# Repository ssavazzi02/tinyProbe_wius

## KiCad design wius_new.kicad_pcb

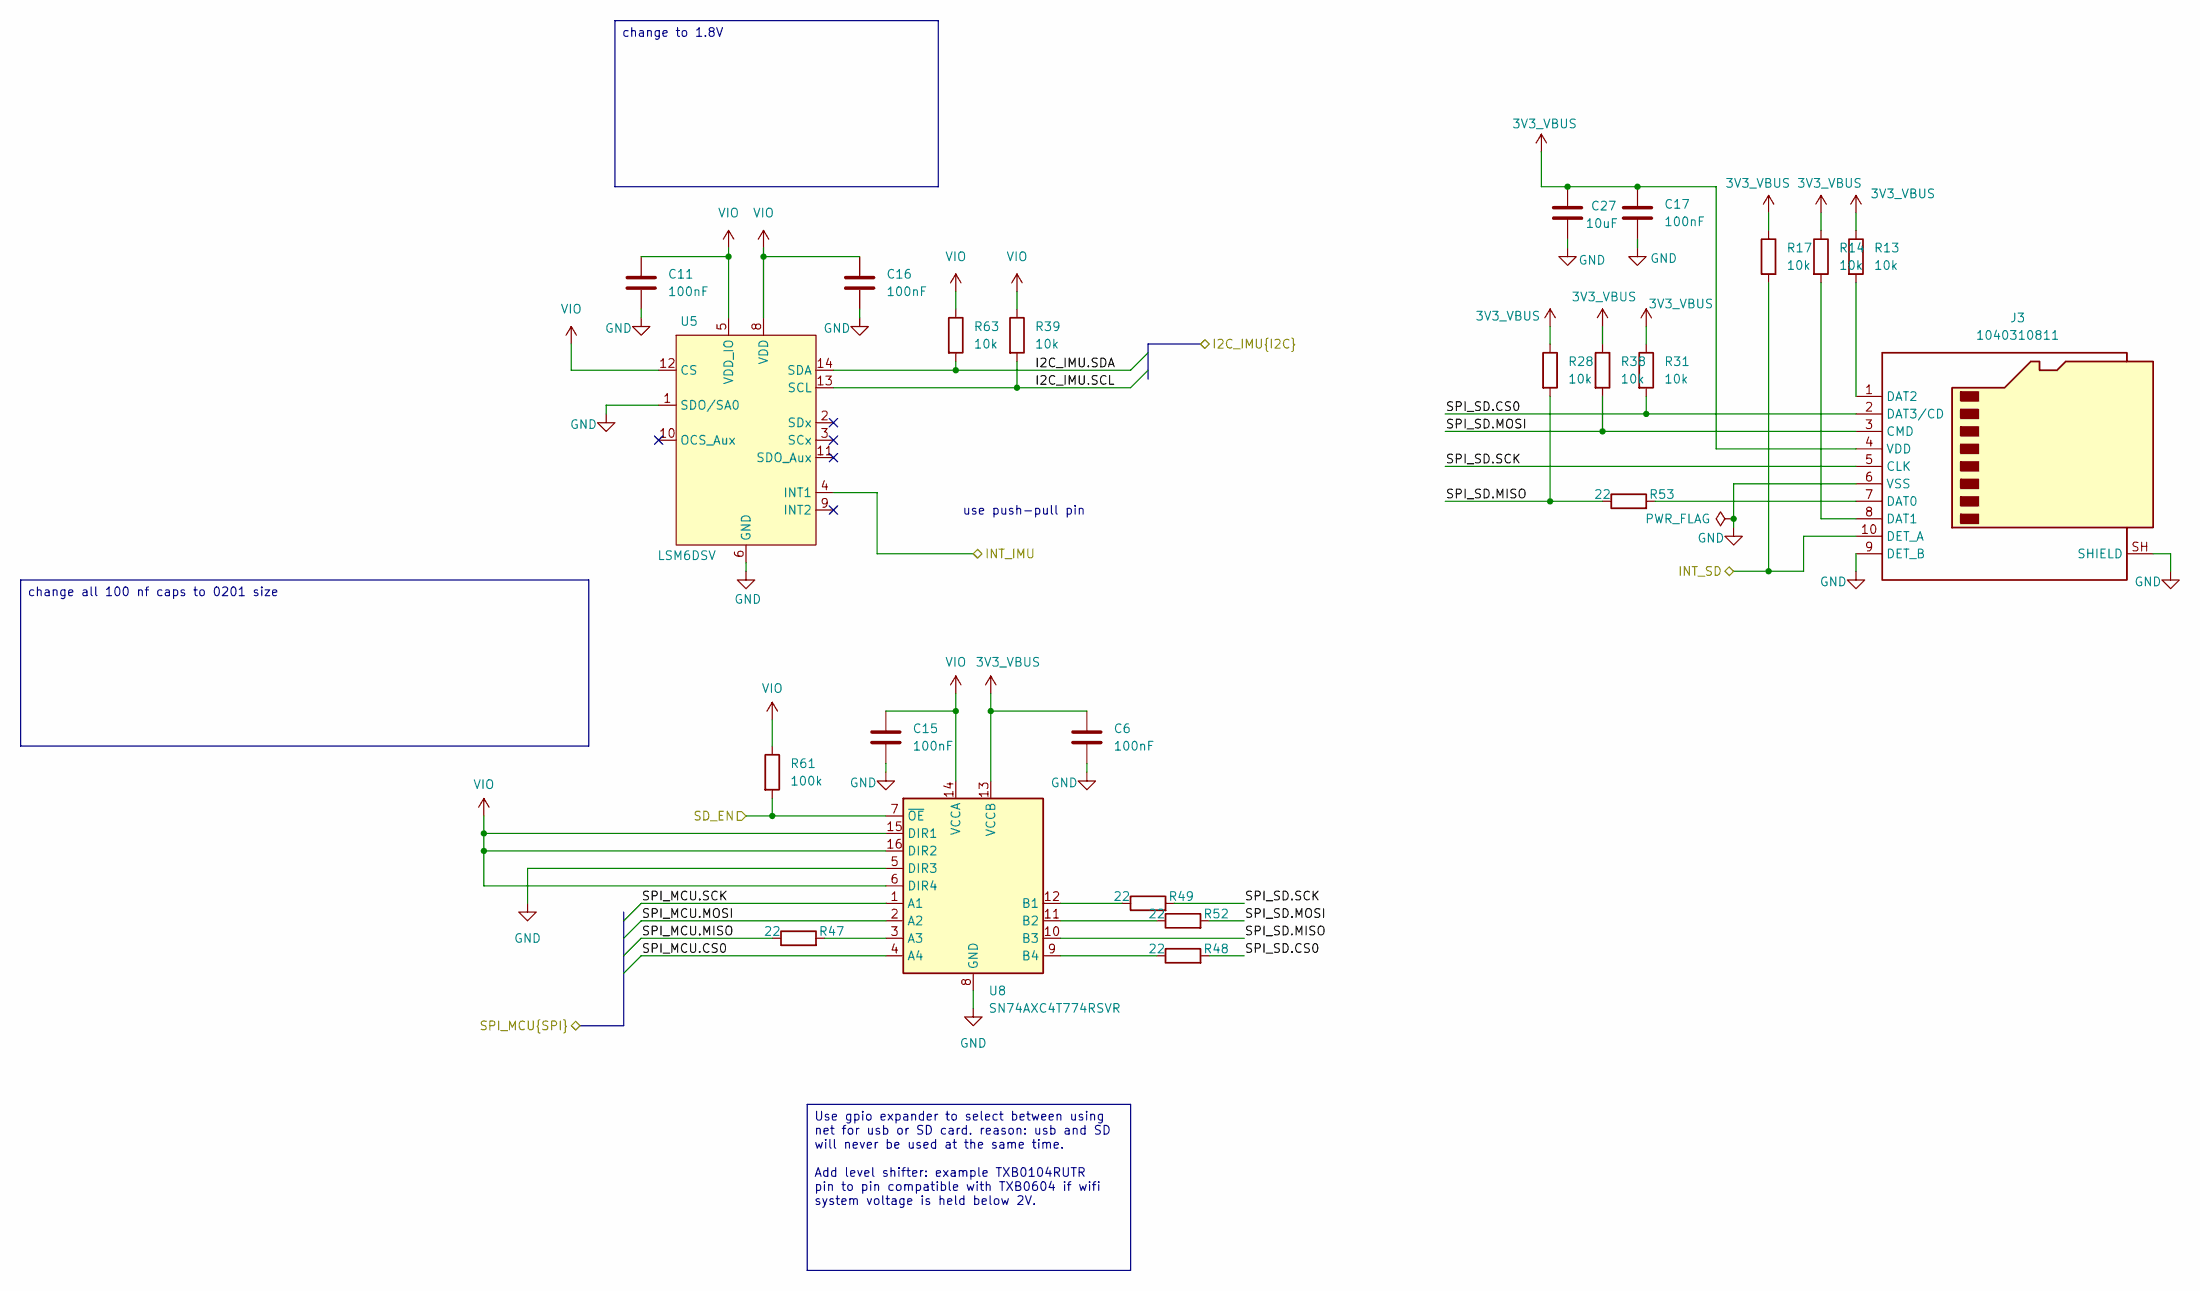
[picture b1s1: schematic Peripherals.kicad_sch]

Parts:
C6, C11, C15, C16, C17: 100nF; C_0201_0603Metric; Voltage 10V; Tolerance 20%; MPN GRM033R61A104ME15
C27: 10uF; C_0603_1608Metric; Voltage 10V; Tolerance 20%; MPN GRM188R61A106ME69; LCSC C197020603
J3: 1040310811; microSD_HC_Molex_104031-0811; MPN 1040310811; LCSC C585350
R13, R14, R17, R28, R31, R38, R39, R63: 10k; R_0201_0603Metric; Tolerance 1%; MPN ERJ-1GJF1002C; LCSC C20021044
R47, R48, R49, R52, R53: 22; R_0201_0603Metric; Tolerance 1%; MPN ERJ-1GJF22R0C; LCSC C20021234
R61: 100k; R_0201_0603Metric; Tolerance 1%; MPN ERJ-1GJF1003C; LCSC C20021045
U5: LSM6DSV; LGA-14_3x2.5mm_P0.5mm_LayoutBorder3x4y; MPN LSM6DSV; LCSC C5267399
U8: SN74AXC4T774RSVR; UQFN-16_1.8x2.6mm_P0.4mm; MPN SN74AXC4T774RSVR; LCSC C1849454

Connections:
3V3_VBUS: C6.1, C17.1, C27.1, J3.4 (VDD), R13.1, R14.1, R17.1, R28.1, R31.1, R38.1, U8.13 (VCCB); also elsewhere on the board
/IMU_SD/I2C_IMU.SCL: R39.2, U5.13 (SCL); also elsewhere on the board
/IMU_SD/I2C_IMU.SDA: R63.2, U5.14 (SDA); also elsewhere on the board
/IMU_SD/INT_IMU: U5.4 (INT1); also elsewhere on the board
/IMU_SD/INT_SD: J3.10 (DET_A), R17.2; also elsewhere on the board
/IMU_SD/SD_EN: R61.2, U8.7 (~OE); also elsewhere on the board
/IMU_SD/SPI_MCU.CS0: U8.4 (A4); also elsewhere on the board
/IMU_SD/SPI_MCU.MISO: R47.1; also elsewhere on the board
/IMU_SD/SPI_MCU.MOSI: U8.2 (A2); also elsewhere on the board
/IMU_SD/SPI_MCU.SCK: U8.1 (A1); also elsewhere on the board
/IMU_SD/SPI_SD.CS0: J3.2 (DAT3/CD), R31.2, R48.2
/IMU_SD/SPI_SD.MISO: R28.2, R53.1, U8.10 (B3)
/IMU_SD/SPI_SD.MOSI: J3.3 (CMD), R38.2, R52.2
/IMU_SD/SPI_SD.SCK: J3.5 (CLK), R49.2
GND: C6.2, C11.2, C15.2, C16.2, C17.2, C27.2, J3.6 (VSS), J3.9 (DET_B), J3.SH (SHIELD), U5.1 (SDO/SA0), U5.6 (GND), U5.7 (GND), U8.5 (DIR3), U8.8 (GND); also elsewhere on the board
unnamed: J3.7 (DAT0), R53.2
unnamed: J3.8 (DAT1), R14.2
unnamed: J3.1 (DAT2), R13.2
unnamed: R47.2, U8.3 (A3)
unnamed: R49.1, U8.12 (B1)
unnamed: R52.1, U8.11 (B2)
unnamed: R48.1, U8.9 (B4)
VIO: C11.1, C15.1, C16.1, R39.1, R61.1, R63.1, U5.5 (VDD_IO), U5.8 (VDD), U5.12 (CS), U8.6 (DIR4), U8.14 (VCCA), U8.15 (DIR1), U8.16 (DIR2); also elsewhere on the board

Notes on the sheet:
use push-pull pin
change to 1.8V
Use gpio expander to select between using net for usb or SD card. reason: usb and SD will never be used at the same time. Add level shifter: example TXB0104RUTR pin to pin compatible with TXB0604 if wifi system voltage is held below 2V.
change all 100 nf caps to 0201 size

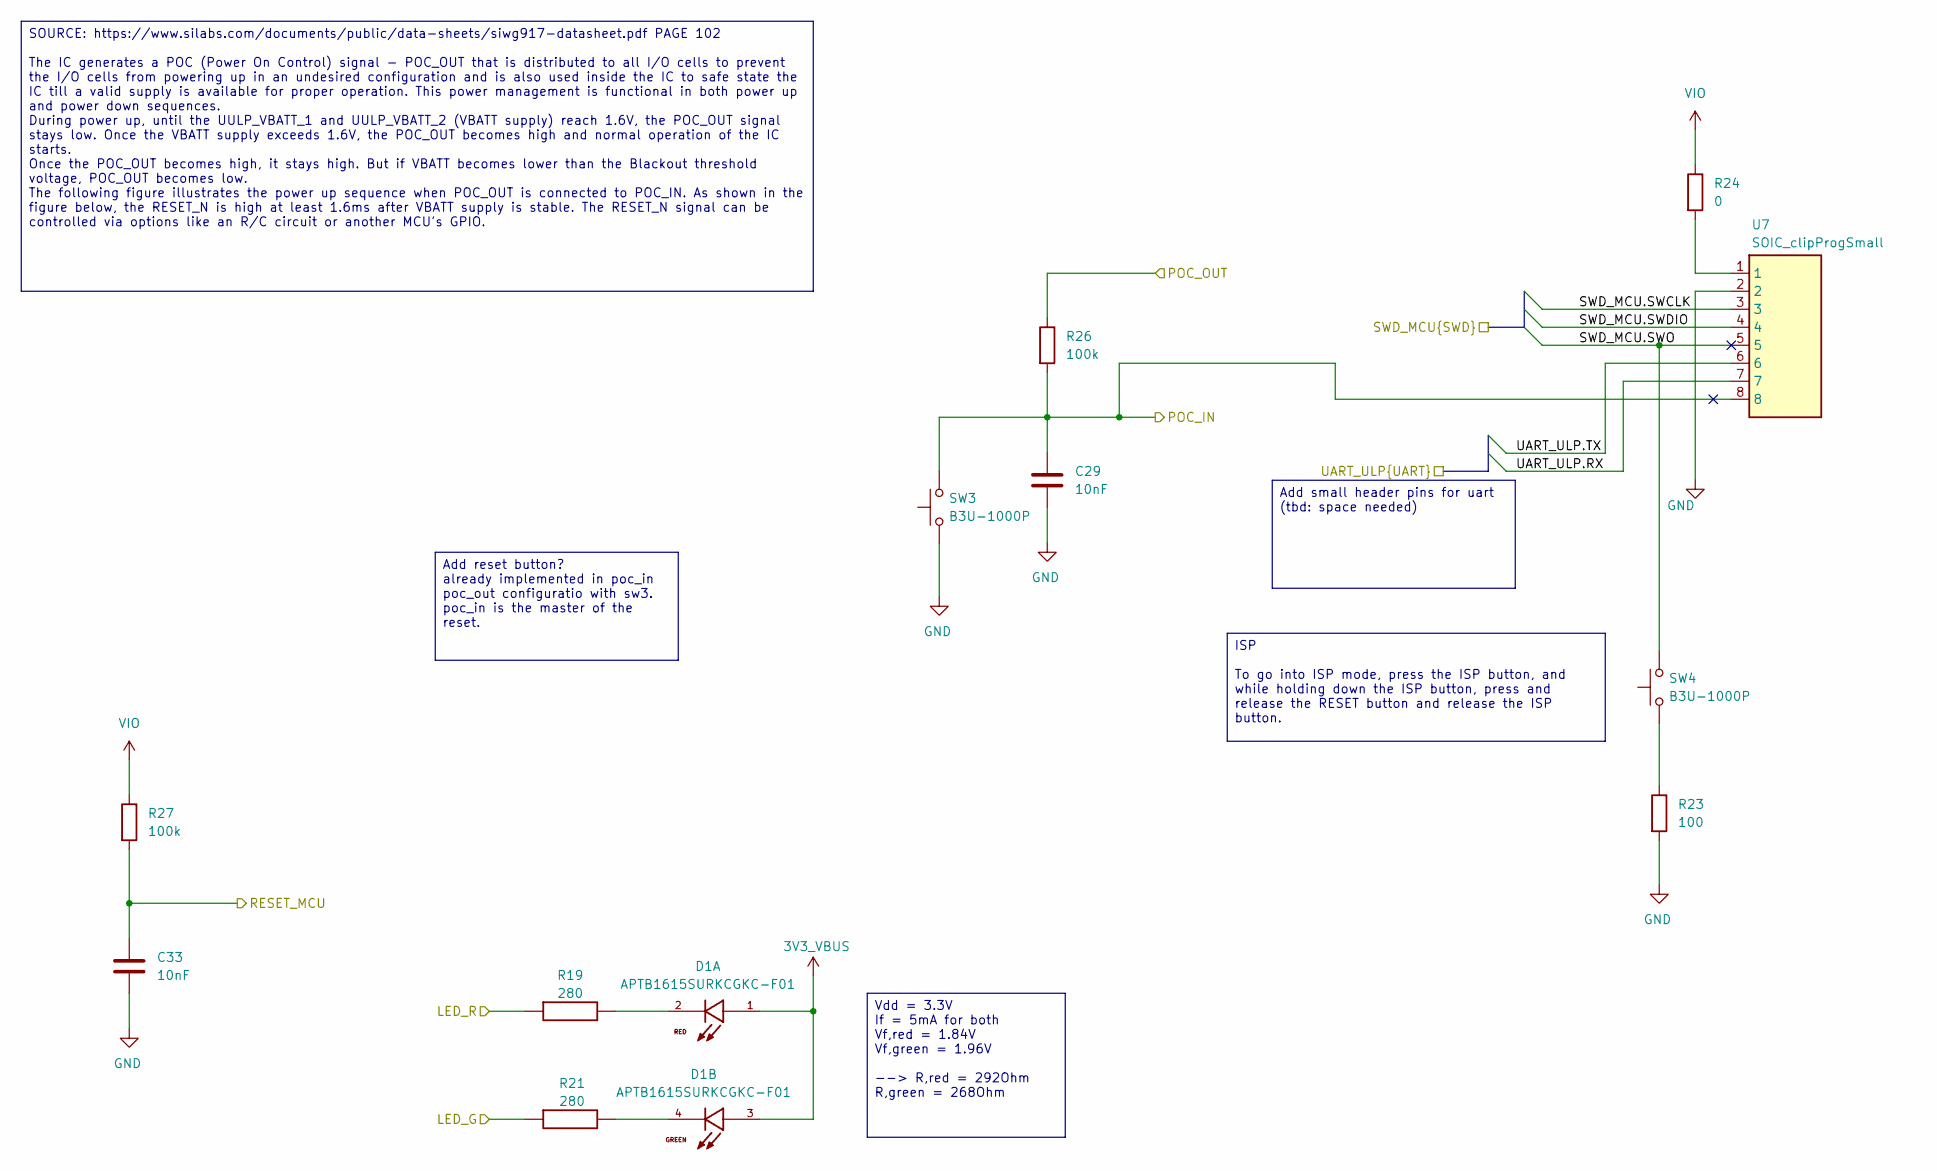
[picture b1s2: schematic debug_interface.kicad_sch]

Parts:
C29, C33: 10nF; C_0402_1005Metric; Tolerance 10%; Voltage 50V; MPN GRM155R71H103KA88J; LCSC C91601
D1: APTB1615SURKCGKC-F01; LED_APTB1615SURKCGKC-F01; MPN APTB1615SURKCGKC-F01; LCSC C5879208
R19, R21: 280; RESC1005X40N; Tolerance 1%; MPN RC0402FR-07280RL; LCSC C273692
R23: 100; R_0402_1005Metric; Tolerance 1%; MPN ERJ-2RKF1000X; LCSC C413063
R24: 0; R_0402_1005Metric; Tolerance 5%; MPN ERJ-2GE0R00X; LCSC C17168
R26, R27: 100k; R_0402_1005Metric; Tolerance 1%; MPN ERJ-2RKF1003X; LCSC C192169
SW3, SW4: Button Switch SPST-No; SW_SPST_B3U-1000P; MPN B3U-1000P; LCSC C231329
U7: SOIC_clipProgSmall

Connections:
3V3_VBUS: D1.1, D1.3; also elsewhere on the board
/DEBUG, RESET & POC_IN, PROGRAMMING INTERFACE/LED_G: R21.1; also elsewhere on the board
/DEBUG, RESET & POC_IN, PROGRAMMING INTERFACE/LED_R: R19.1; also elsewhere on the board
/DEBUG, RESET & POC_IN, PROGRAMMING INTERFACE/SWD_MCU.SWCLK: U7.3; also elsewhere on the board
/DEBUG, RESET & POC_IN, PROGRAMMING INTERFACE/SWD_MCU.SWDIO: U7.4; also elsewhere on the board
/DEBUG, RESET & POC_IN, PROGRAMMING INTERFACE/SWD_MCU.SWO: SW4.2, U7.5; also elsewhere on the board
/DEBUG, RESET & POC_IN, PROGRAMMING INTERFACE/UART_ULP.RX: U7.7; also elsewhere on the board
/DEBUG, RESET & POC_IN, PROGRAMMING INTERFACE/UART_ULP.TX: U7.6; also elsewhere on the board
/MCU/MCU_POWER_RF/POC_IN: C29.1, R26.2, SW3.2, U7.8; also elsewhere on the board
/MCU/MCU_POWER_RF/POC_OUT: R26.1; also elsewhere on the board
/MCU/MCU_POWER_RF/RESET_MCU: C33.1, R27.2; also elsewhere on the board
GND: C29.2, C33.2, R23.2, SW3.1, U7.2; also elsewhere on the board
unnamed: D1.2, R19.2
unnamed: D1.4, R21.2
unnamed: R23.1, SW4.1
unnamed: R24.2, U7.1
VIO: R24.1, R27.1; also elsewhere on the board

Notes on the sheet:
Vdd = 3.3V If = 5mA for both Vf,red = 1.84V Vf,green = 1.96V --> R,red = 292Ohm R,green = 268Ohm
Add reset button? already implemented in poc_in poc_out configuratio with sw3. poc_in is the master of the reset.
Add small header pins for uart (tbd: space needed)
SOURCE: https://www.silabs.com/documents/public/data-sheets/siwg917-datasheet.pdf PAGE 102 The IC generates a POC (Power On Control) signal - POC_OUT that is distributed to all I/O cells to prevent the I/O cells from powering up in an undesired configuration and is also used inside the IC to safe s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
ISP To go into ISP mode, press the ISP button, and while holding down the ISP button, press and release the RESET button and release the ISP button.

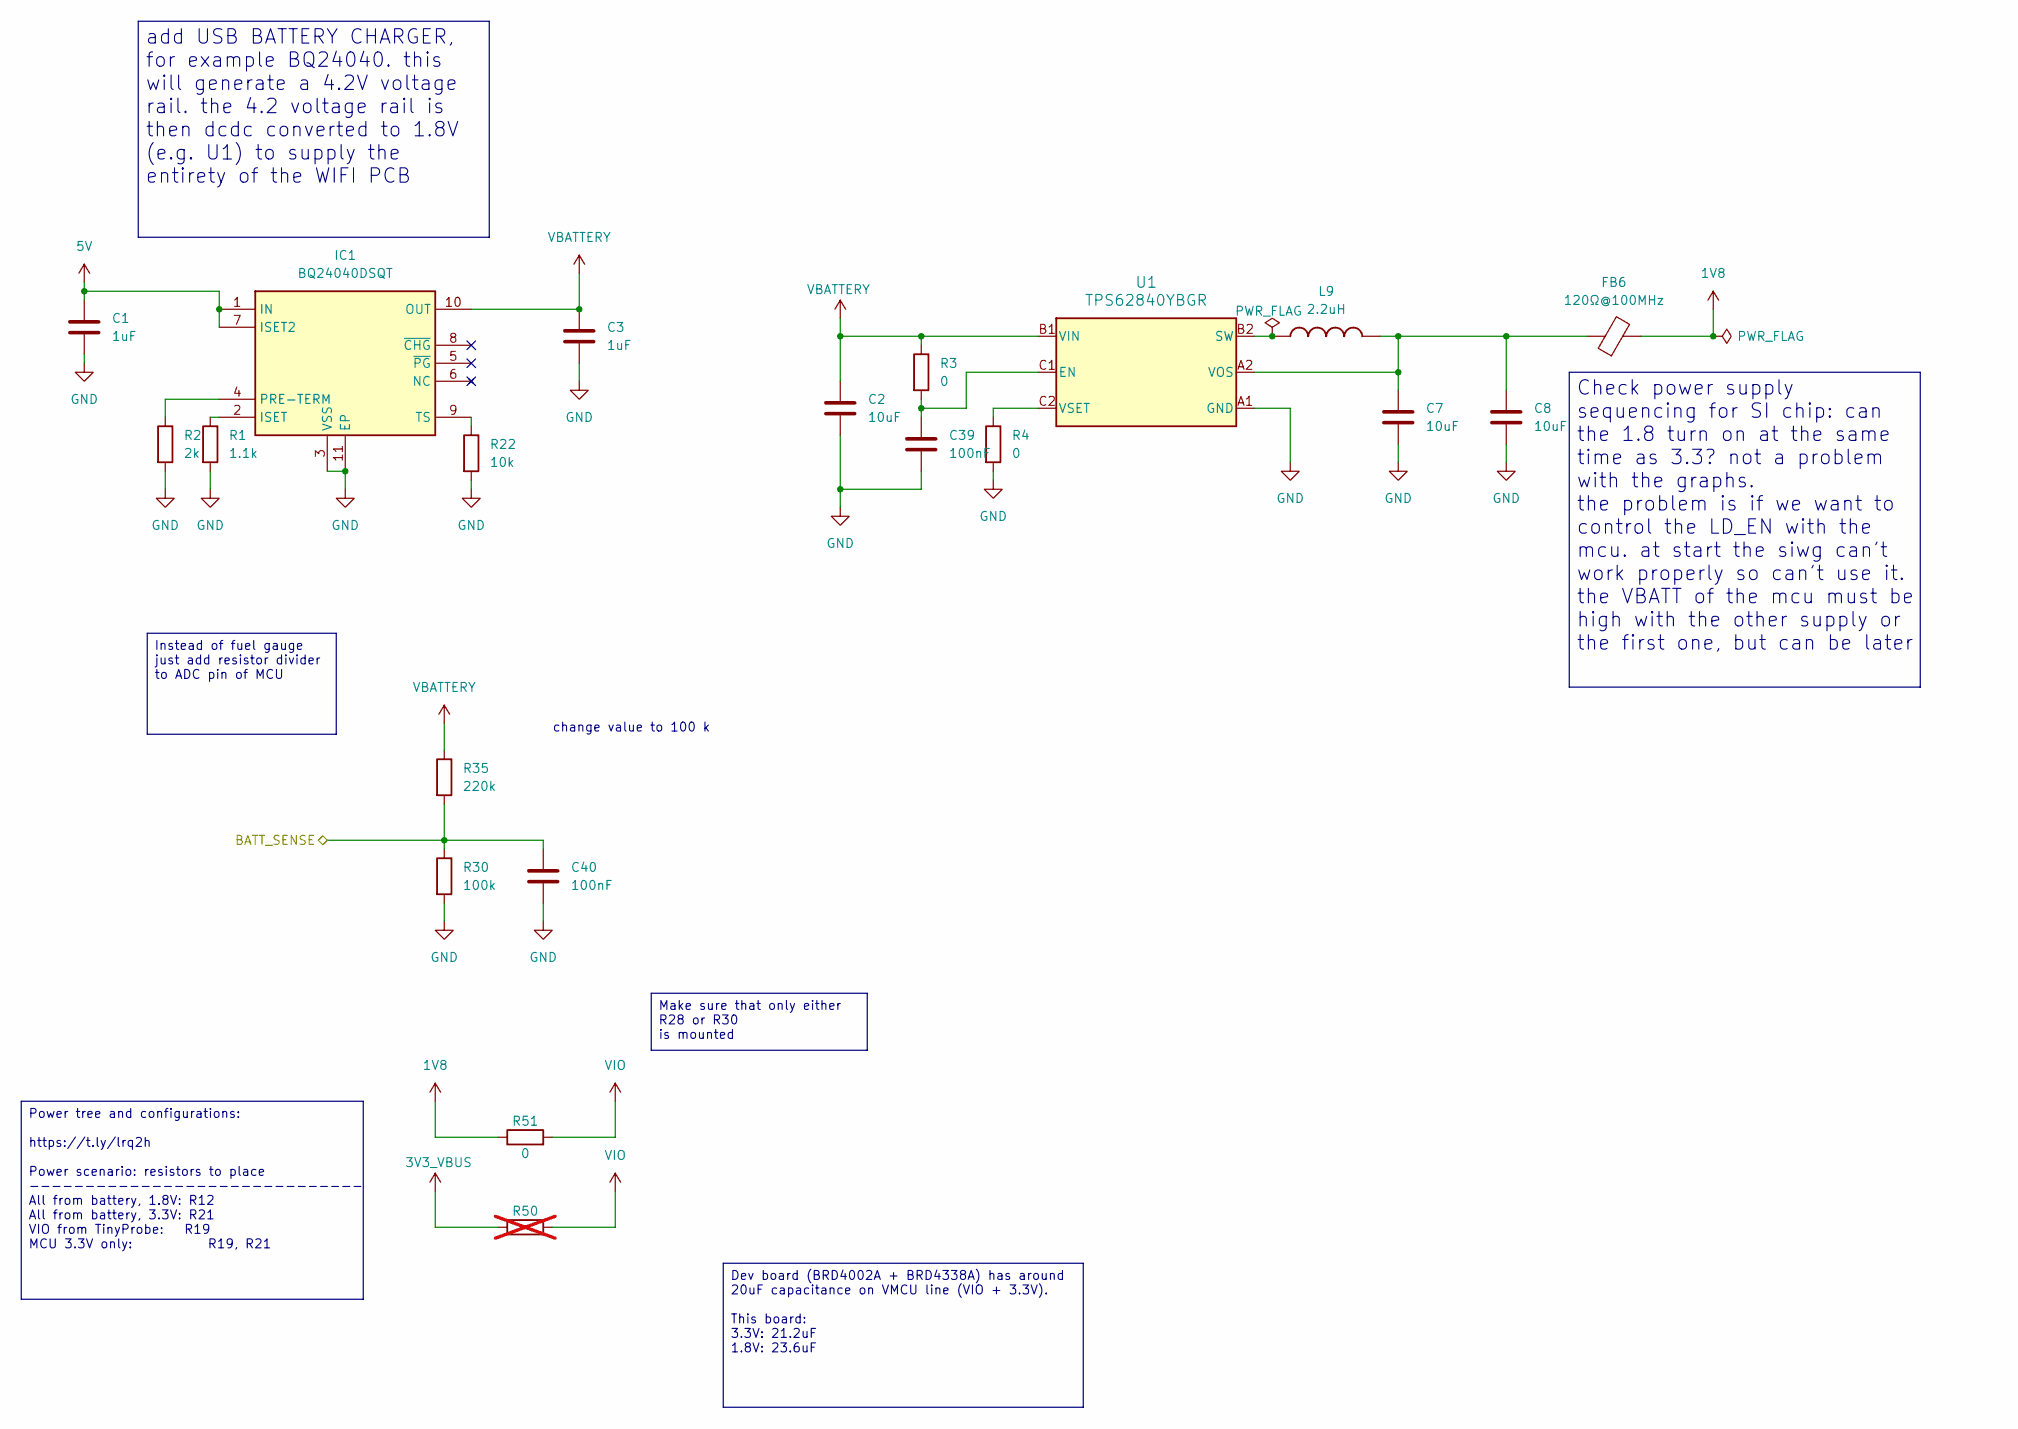
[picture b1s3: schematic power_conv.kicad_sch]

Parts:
C1, C3: 1uF; C_0402_1005Metric; Voltage 16V; Tolerance 20%; MPN GRM155R61C105MA12; LCSC C77009
C2, C7, C8: 10uF; C_0603_1608Metric; Voltage 10V; Tolerance 20%; MPN GRM188R61A106ME69; LCSC C197020603
C39, C40: 100nF; C_0201_0603Metric; Voltage 10V; Tolerance 20%; MPN GRM033R61A104ME15
FB6: 120Ω@100MHz; BLM15KD121SN1D; MPN BLM15KD121SN1D; LCSC C710343
IC1: BQ24040DSQT; MPN BQ24040DSQT; LCSC C2876332
L9: 2.2uH; DFE2MCAH2R2MJ0L; MPN DFE2MCAH2R2MJ0L; LCSC C2045354
R1: 1.1k; R_0402_1005Metric; Tolerance 0.1%; MPN RT0402BRE071K1L; LCSC C853096
R2: 2k; R_0402_1005Metric; Tolerance 0.5%; MPN RT0402DRD072KL; LCSC C853619
R3, R4, R51: 0; R_0402_1005Metric; Tolerance 5%; MPN ERJ-2GE0R00X; LCSC C17168
R22: 10k; R_0402_1005Metric; Tolerance 1%; MPN ERJ-2RKF1002X; LCSC C191123
R30: 100k; R_0402_1005Metric; Tolerance 1%; MPN ERJ-2RKF1003X; LCSC C192169
R35: 220k; R_0402_1005Metric; Tolerance 1%; MPN ERJ-2RKF2203X; LCSC C413112
R50: 0; R_0402_1005Metric; Tolerance 5%; MPN ERJ-2GE0R00X; LCSC C17168; not fitted
U1: TPS62840YBGR; Texas_DSBGA-6_0.9x1.4mm_Layout2x3_P0.5mm; MPN TPS62840YBGR; LCSC 1.5MHz-2.5MHz

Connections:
1V8: FB6.2, R51.1
3V3_VBUS: R50.1; also elsewhere on the board
5V: C1.1, IC1.1 (IN), IC1.7 (ISET2); also elsewhere on the board
/MCU/BATT_SENSE: C40.1, R30.1, R35.2; also elsewhere on the board
GND: C1.2, C2.2, C3.2, C7.2, C8.2, C39.2, C40.2, IC1.3 (VSS), IC1.11 (EP), R1.2, R2.2, R4.2, R22.2, R30.2, U1.A1 (GND); also elsewhere on the board
unnamed: IC1.2 (ISET), R1.1
unnamed: IC1.4 (PRE-TERM), R2.1
unnamed: IC1.9 (TS), R22.1
unnamed: C39.1, R3.2, U1.C1 (EN)
unnamed: L9.1, U1.B2 (SW)
unnamed: C7.1, C8.1, FB6.1, L9.2, U1.A2 (VOS)
unnamed: R4.1, U1.C2 (VSET)
VBATTERY: C2.1, C3.1, IC1.10 (OUT), R3.1, R35.1, U1.B1 (VIN); also elsewhere on the board
VIO: R50.2, R51.2; also elsewhere on the board

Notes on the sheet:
change value to 100 k
add USB BATTERY CHARGER, for example BQ24040. this will generate a 4.2V voltage rail. the 4.2 voltage rail is then dcdc converted to 1.8V (e.g. U1) to supply the entirety of the WIFI PCB
Power tree and configurations: https://t.ly/lrq2h Power scenario: resistors to place ------------------------------ All from battery, 1.8V: R12 All from battery, 3.3V: R21 VIO from TinyProbe: R19 MCU 3.3V only: R19, R21
Dev board (BRD4002A + BRD4338A) has around 20uF capacitance on VMCU line (VIO + 3.3V). This board: 3.3V: 21.2uF 1.8V: 23.6uF
Make sure that only either R28 or R30 is mounted
Check power supply sequencing for SI chip: can the 1.8 turn on at the same time as 3.3? not a problem with the graphs. the problem is if we want to control the LD_EN with the mcu. at start the siwg can't work properly so can't use it. the VBATT of the mcu must be high with the other supply or the f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
Instead of fuel gauge just add resistor divider to ADC pin of MCU

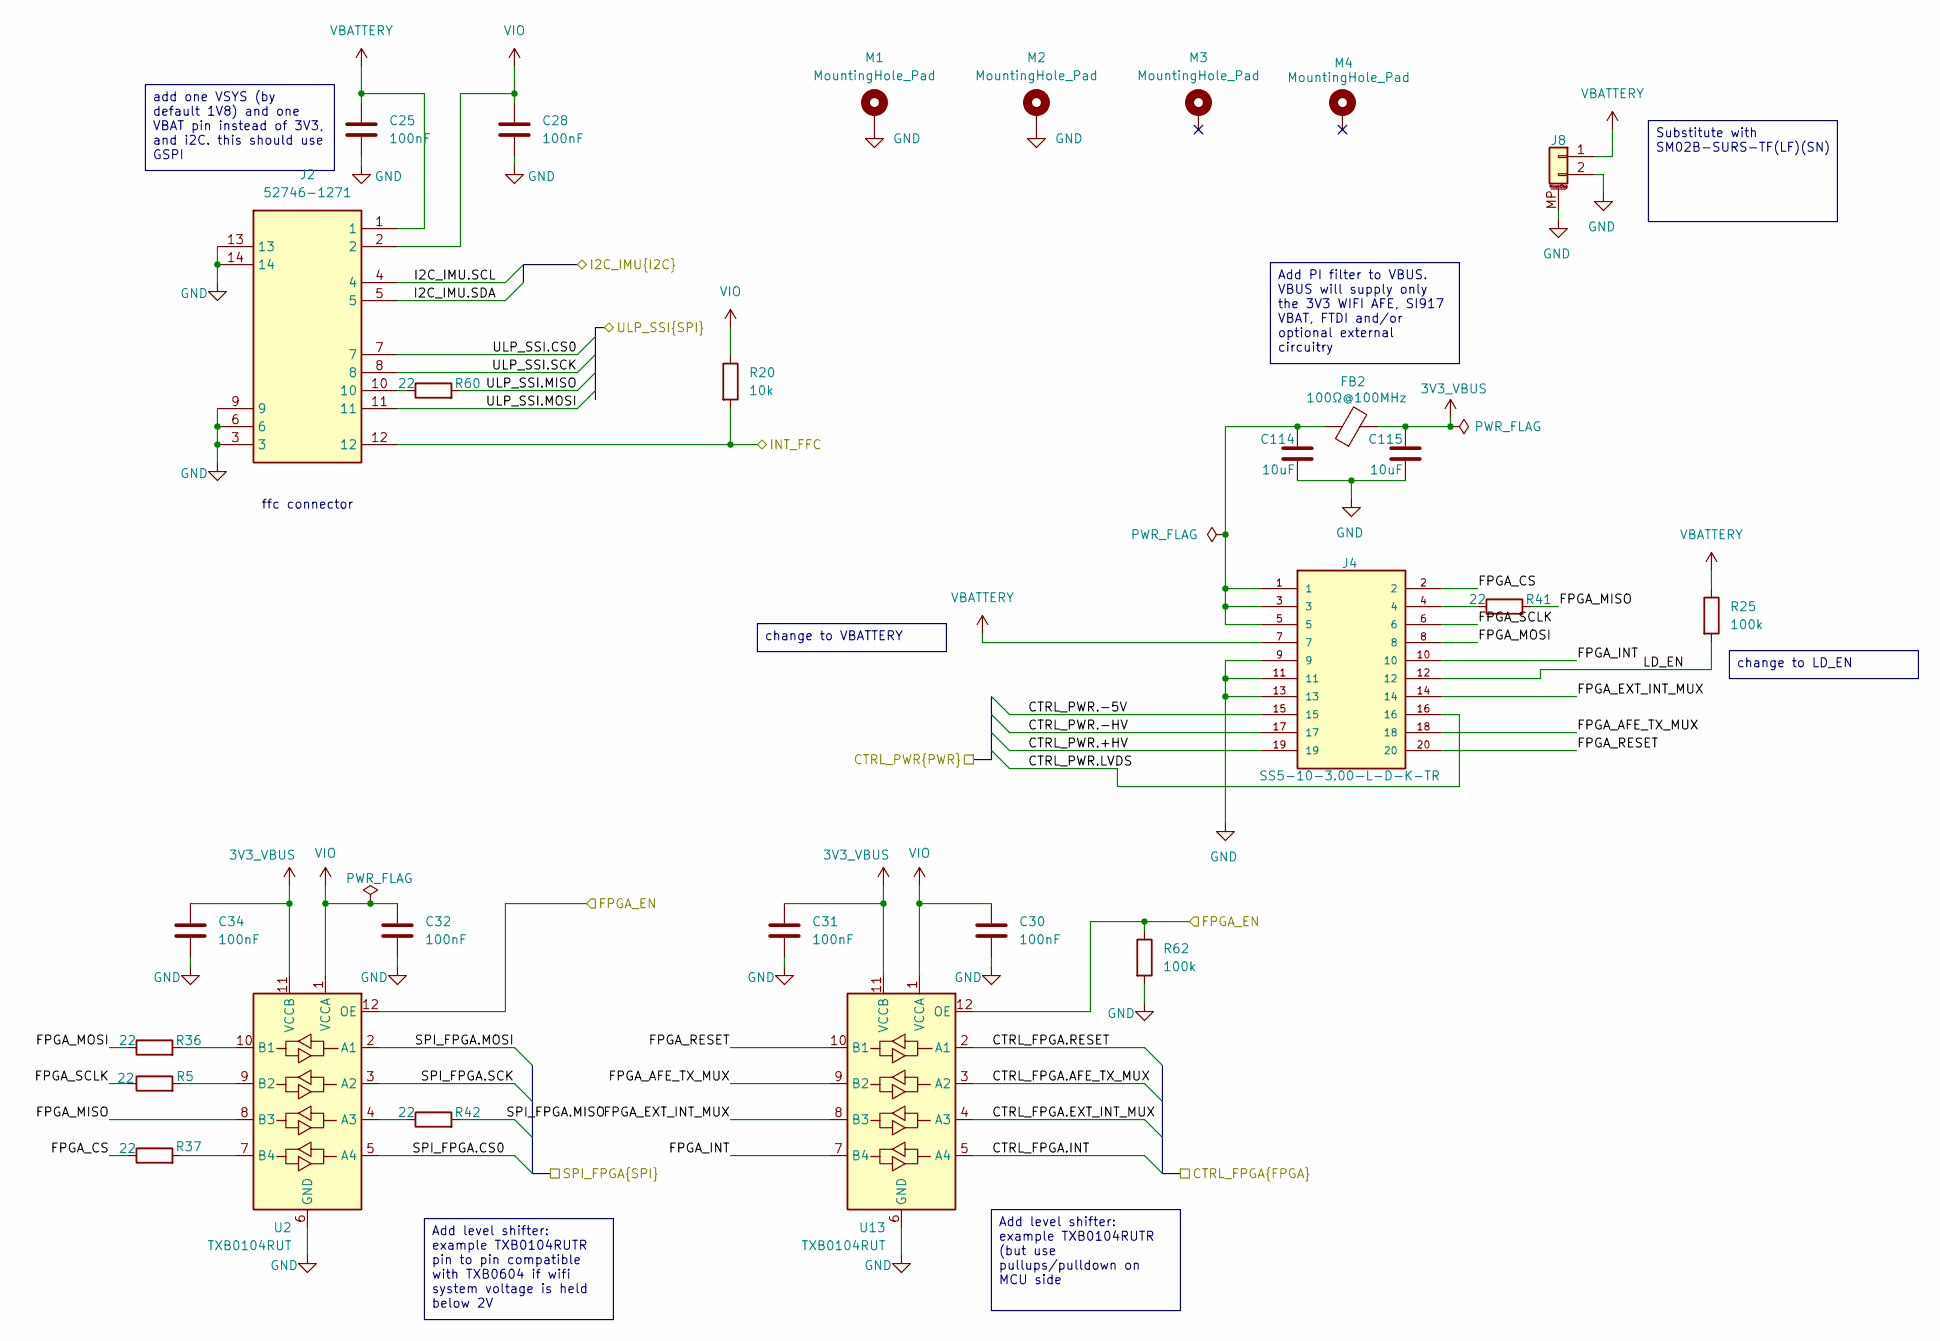
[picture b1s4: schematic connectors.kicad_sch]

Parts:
C25, C28, C30, C31, C32, C34: 100nF; C_0201_0603Metric; Voltage 10V; Tolerance 20%; MPN GRM033R61A104ME15
C114, C115: 10uF; C_0402_1005Metric; Voltage 10V; Tolerance 20%; MPN GRM155R61A106ME11; LCSC C408132
FB2: 100Ω@100MHz; L_0603_1608Metric; MPN BLM18SP101SN1; LCSC C3717002
J2: 52746-1271; 527461271; MPN 52746-1271; LCSC C588231
J4: SS5-10-3.00-L-D-K-TR; SAMTEC_SS5_10_3.00_X_D_K_XX; MPN SS5-10-3.00-L-D-K-TR; LCSC C7087204
J8: 2; JST_SUR_SM02B-SURS-TF_1x02-1MP_P0.80mm_Horizontal; MPN SM02B-SURS-TF(LF)(SN)
M1, M2, M3, M4: MountingHole_Pad; MountingHole_2.4mm_M2_Pad_TopBottom
R5, R36, R37, R41, R42, R60: 22; R_0201_0603Metric; Tolerance 1%; MPN ERJ-1GJF22R0C; LCSC C20021234
R20: 10k; R_0201_0603Metric; Tolerance 1%; MPN ERJ-1GJF1002C; LCSC C20021044
R25: 100k; R_0402_1005Metric; Tolerance 1%; MPN ERJ-2RKF1003X; LCSC C192169
R62: 100k; R_0201_0603Metric; Tolerance 1%; MPN ERJ-1GJF1003C; LCSC C20021045
U2, U13: TXB0104RUT; Texas_R-PUQFN-N12

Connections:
3V3_VBUS: C31.1, C34.1, C115.1, FB2.2, U2.11 (VCCB), U13.11 (VCCB); also elsewhere on the board
/IMU_SD/I2C_IMU.SCL: J2.4; also elsewhere on the board
/IMU_SD/I2C_IMU.SDA: J2.5; also elsewhere on the board
/MCU/CTRL_FPGA.AFE_TX_MUX: U13.3 (A2); also elsewhere on the board
/MCU/CTRL_FPGA.EXT_INT_MUX: U13.4 (A3); also elsewhere on the board
/MCU/CTRL_FPGA.INT: U13.5 (A4); also elsewhere on the board
/MCU/CTRL_FPGA.RESET: U13.2 (A1); also elsewhere on the board
/MCU/CTRL_PWR.+HV: J4.19; also elsewhere on the board
/MCU/CTRL_PWR.-5V: J4.15; also elsewhere on the board
/MCU/CTRL_PWR.-HV: J4.17; also elsewhere on the board
/MCU/CTRL_PWR.LVDS: J4.16; also elsewhere on the board
/MCU/FPGA_EN: R62.1, U2.12 (OE), U13.12 (OE); also elsewhere on the board
/MCU/INT_FFC: J2.12, R20.2; also elsewhere on the board
/MCU/SPI_FPGA.CS0: U2.5 (A4); also elsewhere on the board
/MCU/SPI_FPGA.MISO: R42.2; also elsewhere on the board
/MCU/SPI_FPGA.MOSI: U2.2 (A1); also elsewhere on the board
/MCU/SPI_FPGA.SCK: U2.3 (A2); also elsewhere on the board
/MCU/ULP_SSI.CS0: J2.7; also elsewhere on the board
/MCU/ULP_SSI.MISO: R60.2; also elsewhere on the board
/MCU/ULP_SSI.MOSI: J2.11; also elsewhere on the board
/MCU/ULP_SSI.SCK: J2.8; also elsewhere on the board
/connectors/FPGA_AFE_TX_MUX: J4.18, U13.9 (B2)
/connectors/FPGA_CS: J4.2, R37.1
/connectors/FPGA_EXT_INT_MUX: J4.14, U13.8 (B3)
/connectors/FPGA_INT: J4.10, U13.7 (B4)
/connectors/FPGA_MISO: R41.2, U2.8 (B3)
/connectors/FPGA_MOSI: J4.8, R36.1
/connectors/FPGA_RESET: J4.20, U13.10 (B1)
/connectors/FPGA_SCLK: J4.6, R5.1
/connectors/LD_EN: J4.12, R25.2
GND: C25.2, C28.2, C30.2, C31.2, C32.2, C34.2, C114.2, C115.2, J2.3, J2.6, J2.9, J2.13, J2.14, J4.9, J4.11, J4.13, J8.2, J8.MP (MountPin), M1.1 (1_1), M2.1 (1_1), R62.2, U2.6 (GND), U13.6 (GND); also elsewhere on the board
unnamed: C114.1, FB2.1, J4.1, J4.3, J4.5
unnamed: J2.10, R60.1
unnamed: J4.4, R41.1
unnamed: R42.1, U2.4 (A3)
unnamed: R36.2, U2.10 (B1)
unnamed: R5.2, U2.9 (B2)
unnamed: R37.2, U2.7 (B4)
VBATTERY: C25.1, J2.1, J4.7, J8.1, R25.1; also elsewhere on the board
VIO: C28.1, C30.1, C32.1, J2.2, R20.1, U2.1 (VCCA), U13.1 (VCCA); also elsewhere on the board

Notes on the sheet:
ffc connector
Add level shifter: example TXB0104RUTR pin to pin compatible with TXB0604 if wifi system voltage is held below 2V
change to LD_EN
Add PI filter to VBUS. VBUS will supply only the 3V3 WIFI AFE, SI917 VBAT, FTDI and/or optional external circuitry
Substitute with SM02B-SURS-TF(LF)(SN)
add one VSYS (by default 1V8) and one VBAT pin instead of 3V3, and i2C. this should use GSPI
Add level shifter: example TXB0104RUTR (but use pullups/pulldown on MCU side
change to VBATTERY

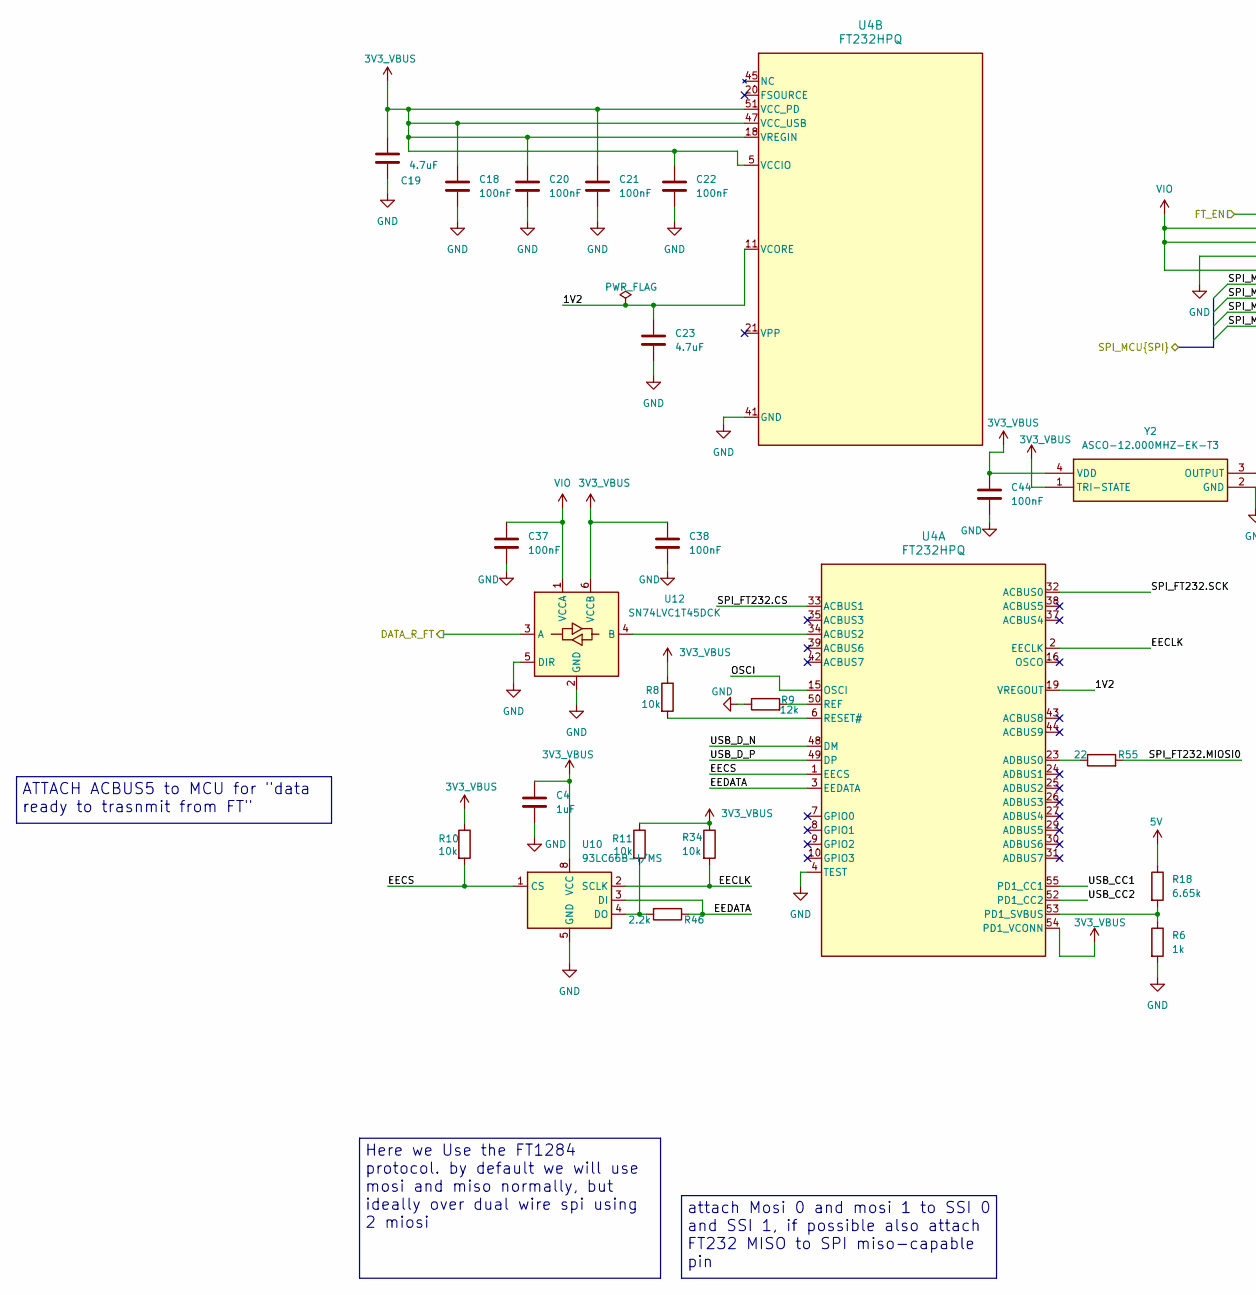
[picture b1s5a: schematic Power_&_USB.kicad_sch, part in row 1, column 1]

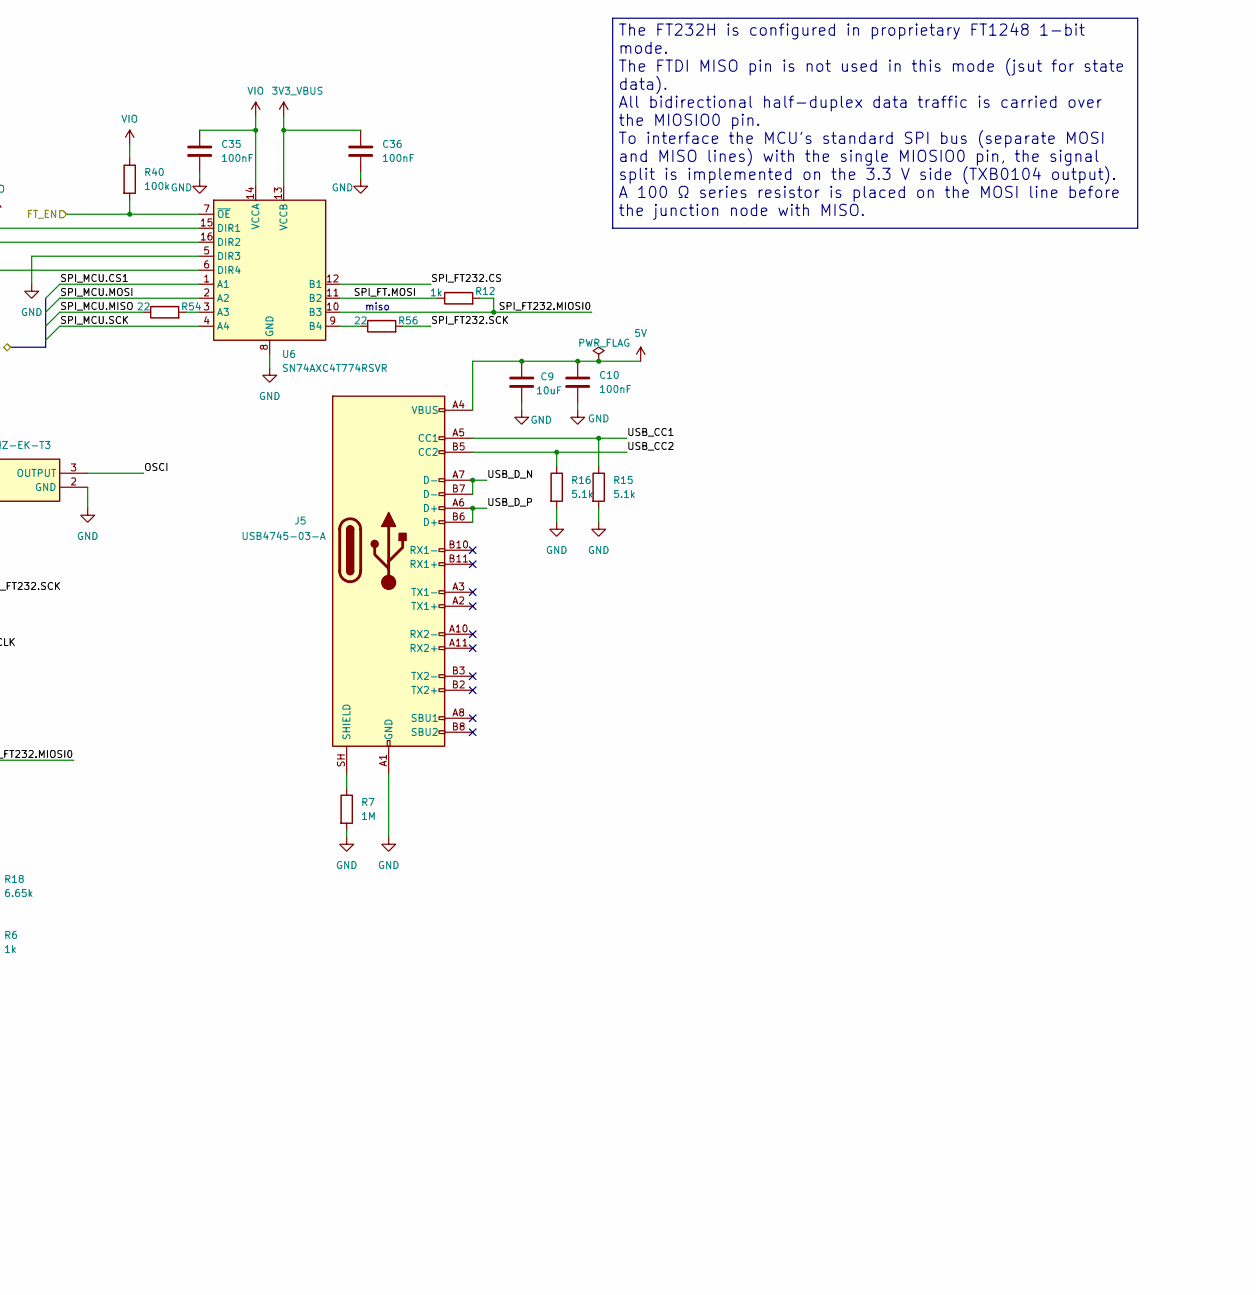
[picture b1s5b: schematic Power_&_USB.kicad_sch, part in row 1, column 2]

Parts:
C4: 1uF; C_0201_0603Metric; Voltage 10V; Tolerance 20%; MPN GRM033R61A105ME15; LCSC C274414
C9: 10uF; C_0603_1608Metric; Voltage 10V; Tolerance 20%; MPN GRM188R61A106ME69; LCSC C197020603
C10, C18, C20, C21, C22, C35, C36, C37, C38, C44: 100nF; C_0201_0603Metric; Voltage 10V; Tolerance 20%; MPN GRM033R61A104ME15
C19, C23: 4.7uF; C_0402_1005Metric; Tolerance 20%; Voltage 25V; MPN GRM155C61E475ME15; LCSC C2858031
J5: USB4745-03-A; GTC_USB4745; MPN USB4745-03-A; LCSC C2911517
R6, R12: 1k; R_0402_1005Metric; Tolerance 1%; MPN ERJ-2RKF1001X; LCSC C242161
R7: 1M; R_0402_1005Metric; Tolerance 1%; MPN ERJ-2RKF1004X; LCSC C413126
R8, R10, R11, R34: 10k; R_0201_0603Metric; Tolerance 1%; MPN ERJ-1GJF1002C; LCSC C20021044
R9: 12k; R_0201_0603Metric; Tolerance 1%; MPN ERJ-1GJF1202C; LCSC C20021084
R15, R16: 5.1k; R_0402_1005Metric; Tolerance 1%; MPN ERJ-2RKF5101X; LCSC C278598
R18: 6.65k; R_0402_1005Metric; Tolerance 1%; MPN RC0402FR-076K65L; LCSC C185400
R40: 100k; R_0201_0603Metric; Tolerance 1%; MPN ERJ-1GJF1003C; LCSC C20021045
R46: 2.2k; R_0201_0603Metric; Tolerance 1%; MPN ERJ-1GJF2201C; LCSC C20021223
R54, R55, R56: 22; R_0201_0603Metric; Tolerance 1%; MPN ERJ-1GJF22R0C; LCSC C20021234
U4: FT232HPQ; QFN-56_FT232HPQ_FTD; MPN FT232HPQ; LCSC C3227934
U6: SN74AXC4T774RSVR; UQFN-16_1.8x2.6mm_P0.4mm; MPN SN74AXC4T774RSVR; LCSC C1849454
U10: 93LC66B-I/MS; MSOP8_MC_MCH; MPN 93LC66B-I/MS
U12: SN74LVC1T45DCK; SOT-363_SC-70-6
Y2: ASCO-12.000MHZ-EK-T3; Oscillator_SMD_Abracon_ASCO-4Pin_1.6x1.2mm; MPN ASCO-12.000MHZ-EK-T3; Mouser Part Number 815-ASCO-12-EK-T3

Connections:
3V3_VBUS: C4.1, C18.1, C19.1, C20.1, C21.1, C22.1, C36.1, C38.1, C44.1, R8.1, R10.1, R11.1, R34.1, U4.5 (VCCIO), U4.13 (VCCIO), U4.14 (VCCIO), U4.18 (VREGIN), U4.28 (VCCIO), U4.40 (VCCIO), U4.47 (VCC_USB), U4.51 (VCC_PD), U4.54 (PD1_VCONN), U6.13 (VCCB), U10.8 (VCC), U12.6 (VCCB), Y2.1 (TRI-STATE), Y2.4 (VDD); also elsewhere on the board
5V: C9.1, C10.1, J5.A4 (VBUS), J5.A9 (VBUS), J5.B4 (VBUS), J5.B9 (VBUS), R18.1; also elsewhere on the board
/IMU_SD/SPI_MCU.CS1: U6.1 (A1); also elsewhere on the board
/IMU_SD/SPI_MCU.MISO: R54.1; also elsewhere on the board
/IMU_SD/SPI_MCU.MOSI: U6.2 (A2); also elsewhere on the board
/IMU_SD/SPI_MCU.SCK: U6.4 (A4); also elsewhere on the board
/MCU/DATA_R_FT: U12.3 (A); also elsewhere on the board
/MCU/FT_EN: R40.2, U6.7 (~OE); also elsewhere on the board
/USB_FT232HPQ/1V2: C23.1, U4.11 (VCORE), U4.19 (VREGOUT), U4.22 (VCORE), U4.36 (VCORE), U4.46 (VCORE), U4.56 (VCORE)
/USB_FT232HPQ/EECLK: R34.2, U4.2 (EECLK), U10.2 (SCLK)
/USB_FT232HPQ/EECS: R10.2, U4.1 (EECS), U10.1 (CS)
/USB_FT232HPQ/EEDATA: R46.1, U4.3 (EEDATA), U10.3 (DI)
/USB_FT232HPQ/OSCI: U4.15 (OSCI), Y2.3 (OUTPUT)
/USB_FT232HPQ/SPI_FT232.CS: U4.33 (ACBUS1), U6.12 (B1)
/USB_FT232HPQ/SPI_FT232.MIOSI0: R12.2, R55.2, U6.10 (B3)
/USB_FT232HPQ/SPI_FT232.SCK: R56.2, U4.32 (ACBUS0)
/USB_FT232HPQ/SPI_FT.MOSI: R12.1, U6.11 (B2)
/USB_FT232HPQ/USB_CC1: J5.A5 (CC1), R15.1, U4.55 (PD1_CC1)
/USB_FT232HPQ/USB_CC2: J5.B5 (CC2), R16.1, U4.52 (PD1_CC2)
/USB_FT232HPQ/USB_D_N: J5.A7 (D-), J5.B7 (D-), U4.48 (DM)
/USB_FT232HPQ/USB_D_P: J5.A6 (D+), J5.B6 (D+), U4.49 (DP)
GND: C4.2, C9.2, C10.2, C18.2, C19.2, C20.2, C21.2, C22.2, C23.2, C35.2, C36.2, C37.2, C38.2, C44.2, J5.A1 (GND), J5.A12 (GND), J5.B1 (GND), J5.B12 (GND), R6.2, R7.2, R9.1, R15.2, R16.2, U4.4 (TEST), U4.12 (GND), U4.17 (GND), U4.41 (GND), U4.57 (GND), U6.5 (DIR3), U6.8 (GND), U10.5 (GND), U12.2 (GND), U12.5 (DIR), Y2.2 (GND); also elsewhere on the board
unnamed: J5.SH (SHIELD), R7.1
unnamed: R55.1, U4.23 (ADBUS0)
unnamed: R6.1, R18.2, U4.53 (PD1_SVBUS)
unnamed: R9.2, U4.50 (REF)
unnamed: R8.2, U4.6 (RESET#)
unnamed: R54.2, U6.3 (A3)
unnamed: R56.1, U6.9 (B4)
unnamed: R11.2, R46.2, U10.4 (DO)
unnamed: U4.34 (ACBUS2), U12.4 (B)
VIO: C35.1, C37.1, R40.1, U6.6 (DIR4), U6.14 (VCCA), U6.15 (DIR1), U6.16 (DIR2), U12.1 (VCCA); also elsewhere on the board

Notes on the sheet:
miso
The FT232H is configured in proprietary FT1248 1-bit mode. The FTDI MISO pin is not used in this mode (jsut for state data). All bidirectional half-duplex data traffic is carried over the MIOSIO0 pin. To interface the MCU's standard SPI bus (separate MOSI and MISO lines) with the single MIOSIO0 pin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
ATTACH ACBUS5 to MCU for "data ready to trasnmit from FT"
attach Mosi 0 and mosi 1 to SSI 0 and SSI 1, if possible also attach FT232 MISO to SPI miso-capable pin
Here we Use the FT1284 protocol. by default we will use mosi and miso normally, but ideally over dual wire spi using 2 miosi
